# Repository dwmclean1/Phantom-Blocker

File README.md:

# Phantom-Blocker
Passive Phantom Power blocking in an XLR barrel

## What is it?

This tiny PCB can be used inline on an XLR mixer input to protect the connected device from accidental enabling of phantom power.

br

It will _just_ fit inside a cheap XLR barrel.

Included are gerbers and CSV BOM which can be used to have the board manufactured with components by JLCPCB.

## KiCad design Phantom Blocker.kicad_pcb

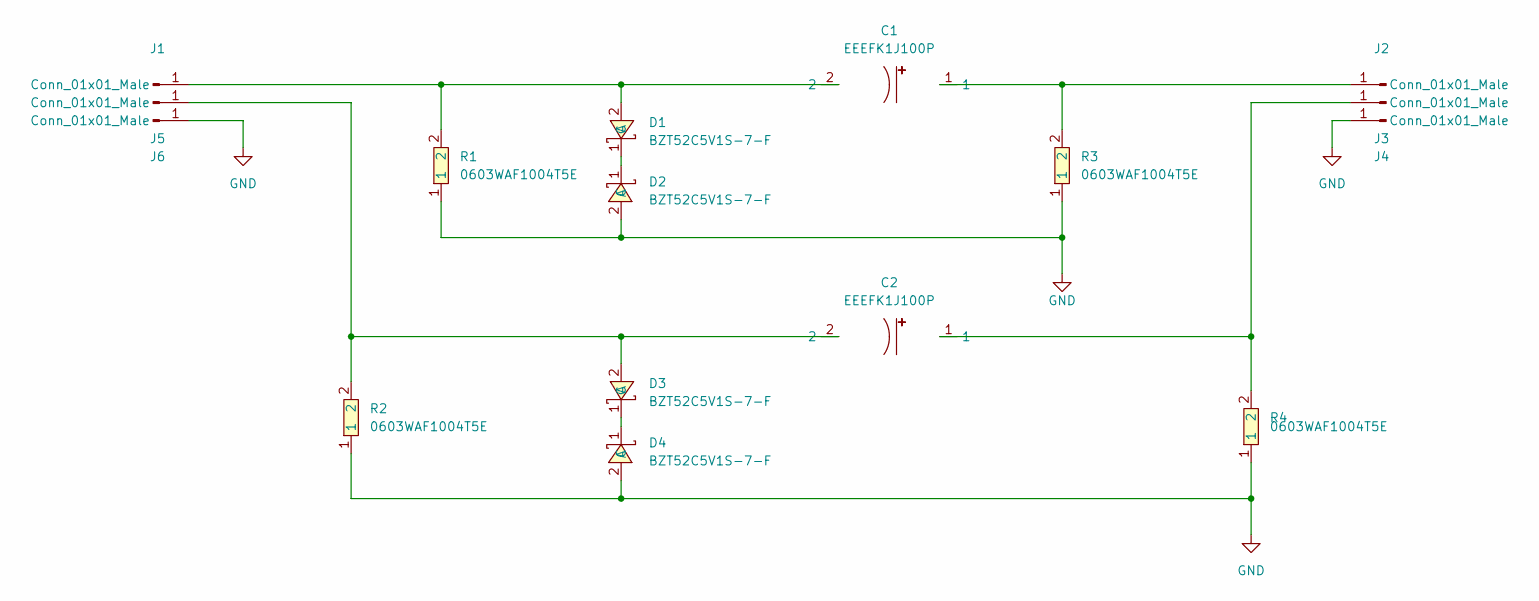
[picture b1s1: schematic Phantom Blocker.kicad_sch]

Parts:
C1, C2: EEEFK1J100P; CAP-SMD_BD6.3-L6.6-W6.6-FD; LCSC Part C128459
D1, D2, D3, D4: BZT52C5V1S-7-F; SOD-323_L1.8-W1.3-LS2.5-RD; LCSC Part C75073
J1, J2, J3, J4, J5, J6: Conn_01x01_Male; Pin_D0.7mm_L6.5mm_W1.8mm_FlatFork
R1, R2, R3, R4: 0603WAF1004T5E; R0603; LCSC Part C22935

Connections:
GND: D2.2 (A), D4.2 (A), J4.1, J6.1, R1.1, R2.1, R3.1, R4.1
unnamed: C1.1, J2.1, R3.2
unnamed: C1.2, D1.2 (A), J1.1, R1.2
unnamed: C2.1, J3.1, R4.2
unnamed: C2.2, D3.2 (A), J5.1, R2.2
unnamed: D1.1 (C), D2.1 (C)
unnamed: D3.1 (C), D4.1 (C)

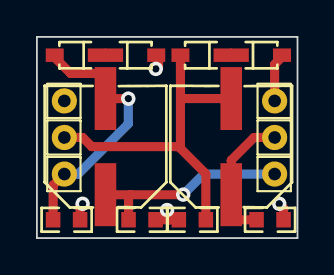
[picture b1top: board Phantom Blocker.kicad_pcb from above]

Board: 2 copper layers, 14.5 x 11.2 mm, 16 parts (0 on the bottom side), 7 nets.
